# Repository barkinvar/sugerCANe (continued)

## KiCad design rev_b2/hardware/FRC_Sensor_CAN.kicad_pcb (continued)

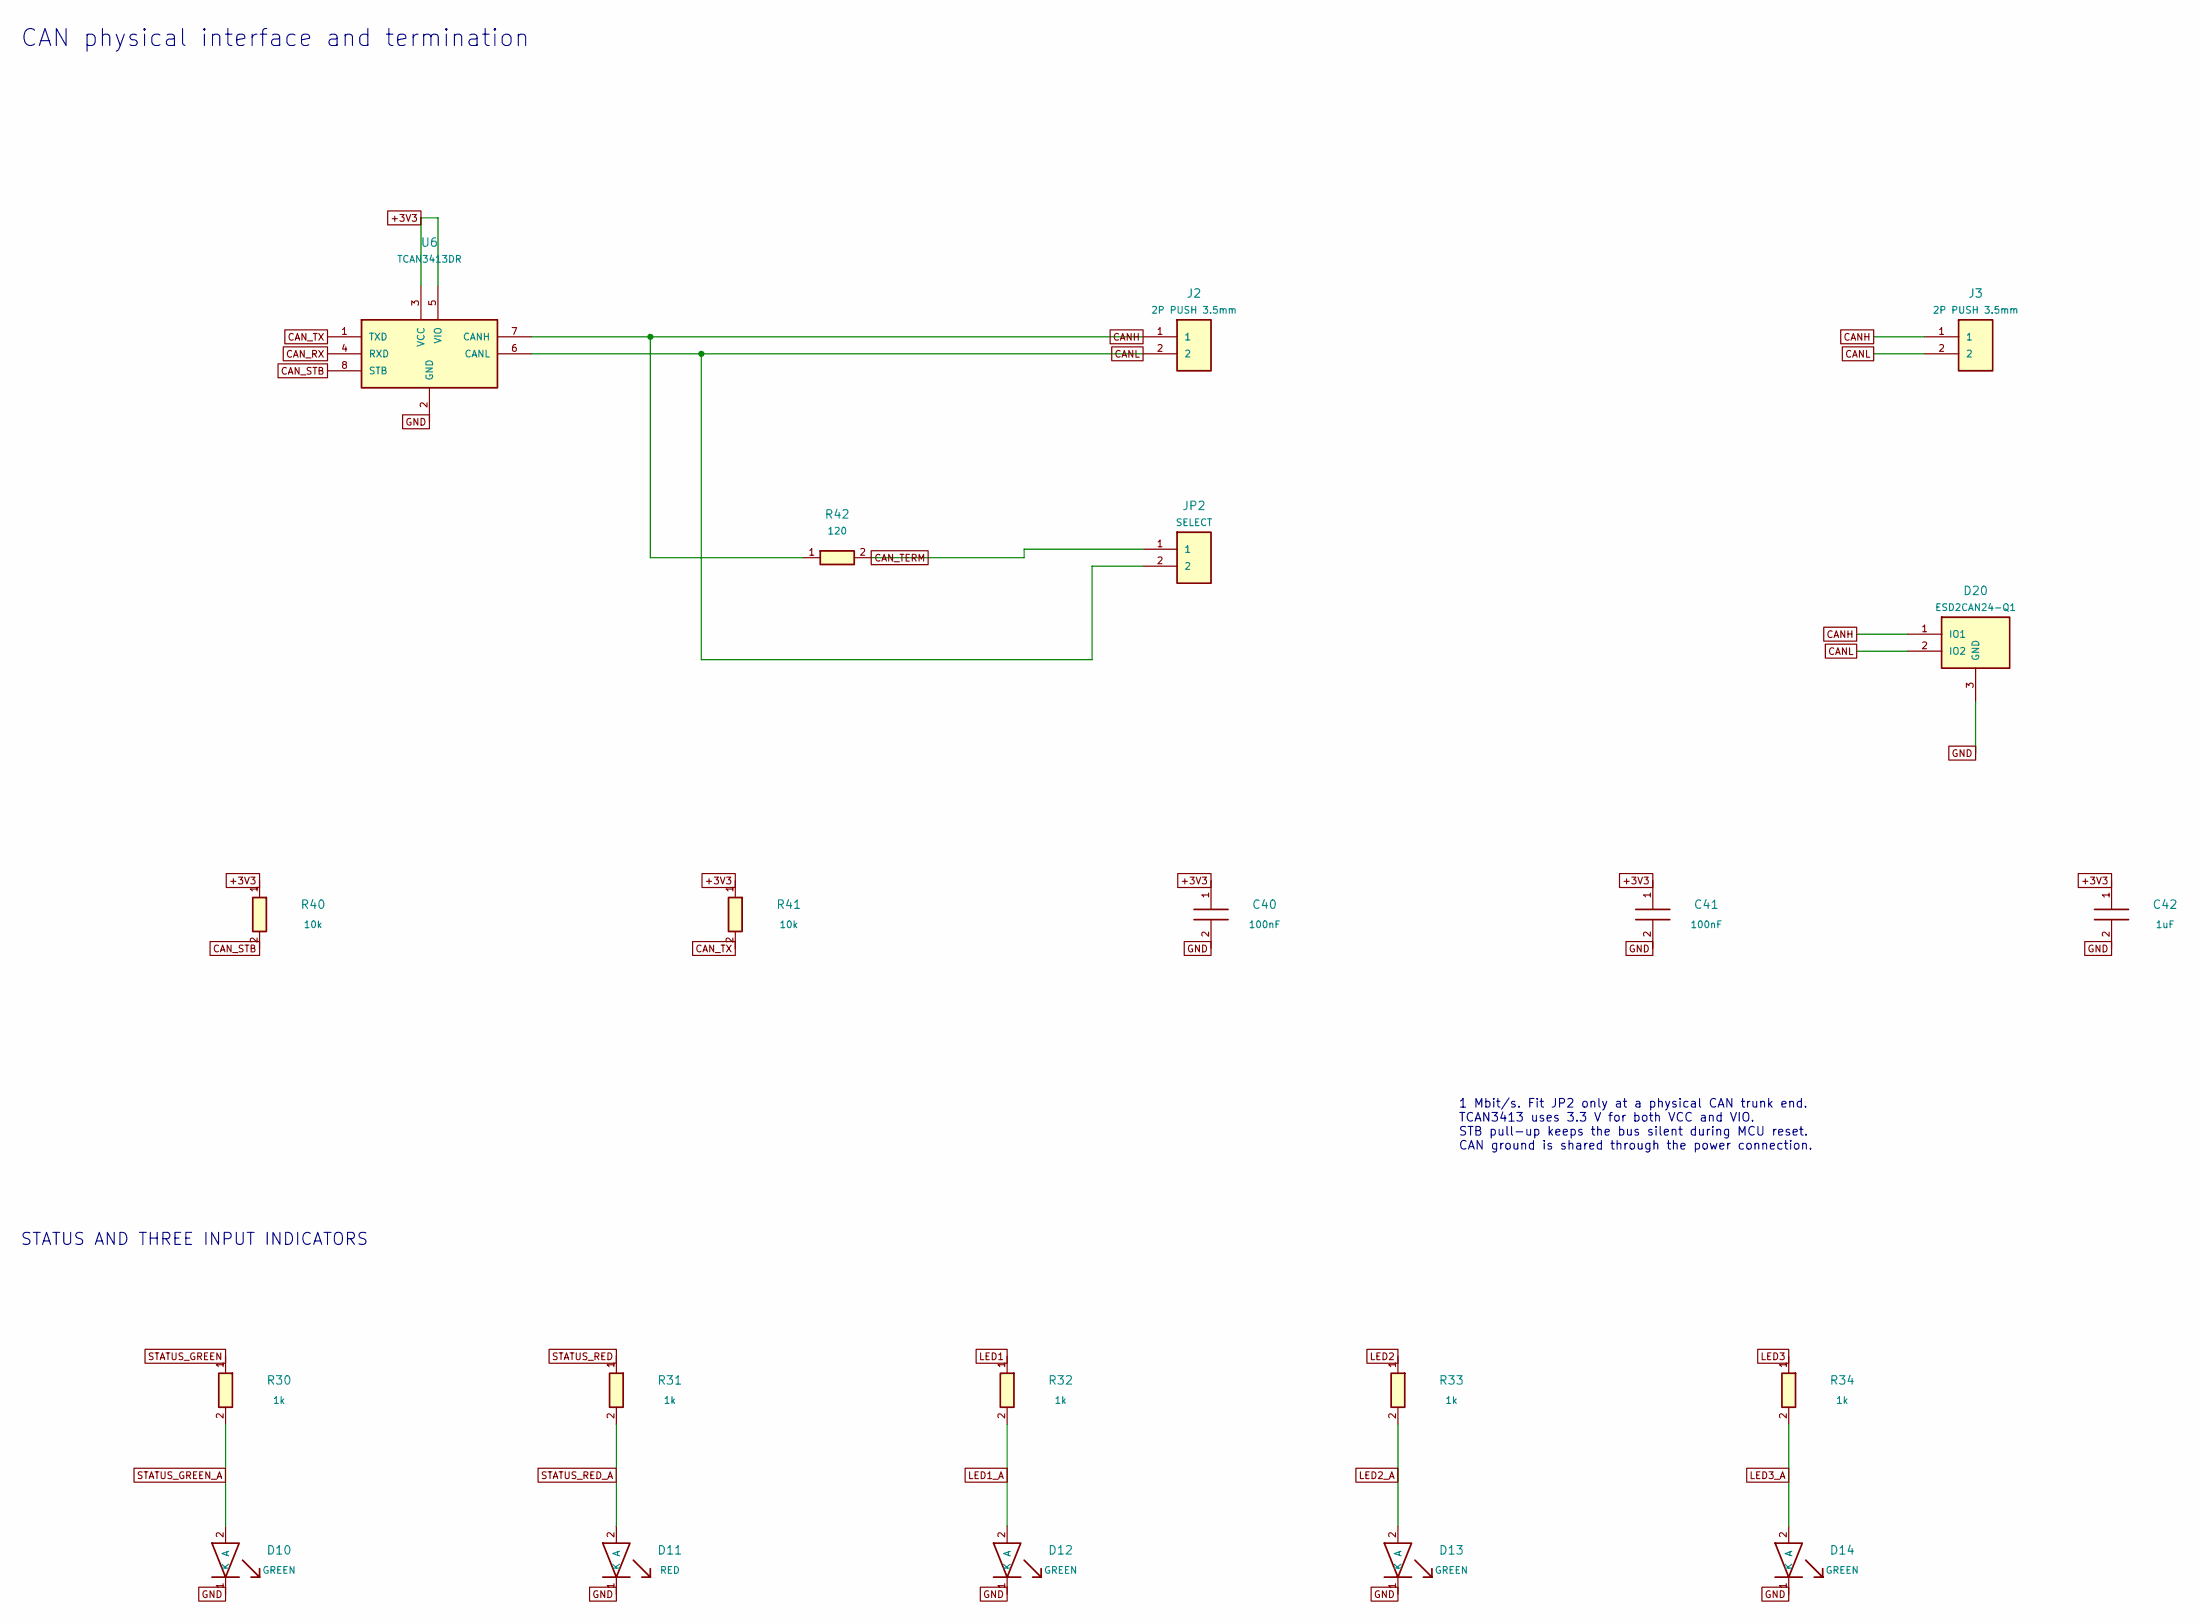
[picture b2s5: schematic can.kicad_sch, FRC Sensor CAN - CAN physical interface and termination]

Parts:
C40, C41: 100nF; C_0805_2012Metric; MPN CL21B104KCFNNNE
C42: 1uF; C_0805_2012Metric; MPN CC0805KKX7R9BB105
D10, D12, D13, D14: GREEN; LED_0805_2012Metric; MPN LTST-C170KGKT
D11: RED; LED_0805_2012Metric; MPN LTST-C170KRKT
D20: ESD2CAN24-Q1; SOT-23; MPN ESD2CAN24DBZRQ1
J2, J3: 2P PUSH 3.5mm; Weidmuller_LSF_90_2P; MPN 1824420000
JP2: SELECT; PinHeader_1x02_P2.00mm_Vertical; MPN M22-2010205
R30, R31, R32, R33, R34: 1k; R_0805_2012Metric; MPN 0805W8F1001T5E
R40, R41: 10k; R_0805_2012Metric; MPN 0805W8F1002T5E
R42: 120; R_1206_3216Metric; MPN RC1206FR-07120RL
U6: TCAN3413DR; SOIC-8_3.9x4.9mm_P1.27mm; MPN TCAN3413DR

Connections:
+3V3: C40.1, C41.1, C42.1, R40.1, R41.1, U6.3 (VCC), U6.5 (VIO); also elsewhere on the board
CANH: D20.1 (IO1), J2.1, J3.1, R42.1, U6.7 (CANH)
CANL: D20.2 (IO2), J2.2, J3.2, JP2.2, U6.6 (CANL)
CAN_RX: U6.4 (RXD); also elsewhere on the board
CAN_STB: R40.2, U6.8 (STB); also elsewhere on the board
CAN_TERM: JP2.1, R42.2
CAN_TX: R41.2, U6.1 (TXD); also elsewhere on the board
GND: C40.2, C41.2, C42.2, D10.1 (K), D11.1 (K), D12.1 (K), D13.1 (K), D14.1 (K), D20.3 (GND), U6.2 (GND); also elsewhere on the board
LED1: R32.1; also elsewhere on the board
LED1_A: D12.2 (A), R32.2
LED2: R33.1; also elsewhere on the board
LED2_A: D13.2 (A), R33.2
LED3: R34.1; also elsewhere on the board
LED3_A: D14.2 (A), R34.2
STATUS_GREEN: R30.1; also elsewhere on the board
STATUS_GREEN_A: D10.2 (A), R30.2
STATUS_RED: R31.1; also elsewhere on the board
STATUS_RED_A: D11.2 (A), R31.2

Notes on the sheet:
CAN physical interface and termination
1 Mbit/s. Fit JP2 only at a physical CAN trunk end. TCAN3413 uses 3.3 V for both VCC and VIO. STB pull-up keeps the bus silent during MCU reset. CAN ground is shared through the power connection.
STATUS AND THREE INPUT INDICATORS

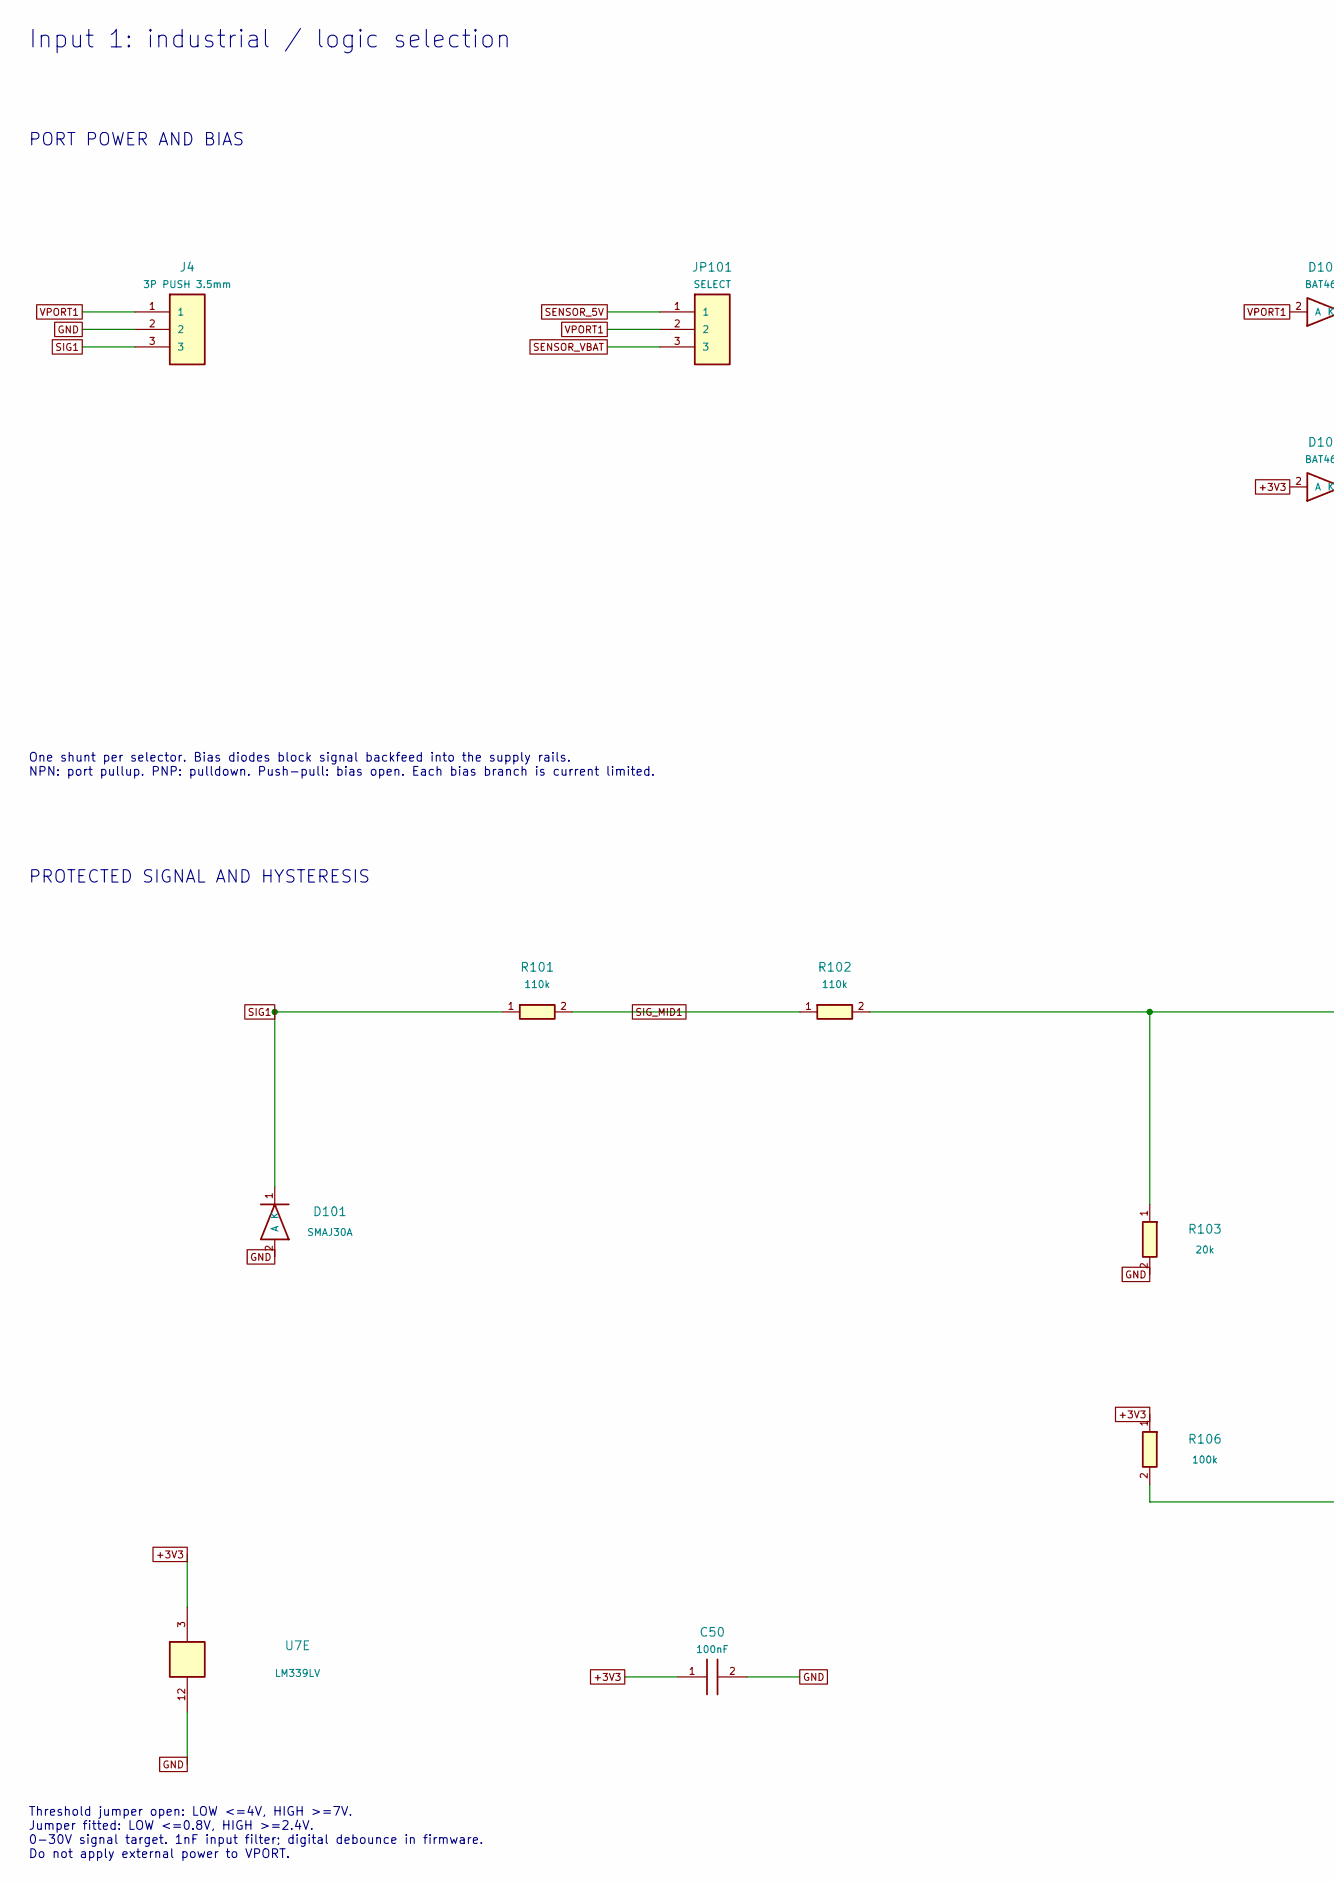
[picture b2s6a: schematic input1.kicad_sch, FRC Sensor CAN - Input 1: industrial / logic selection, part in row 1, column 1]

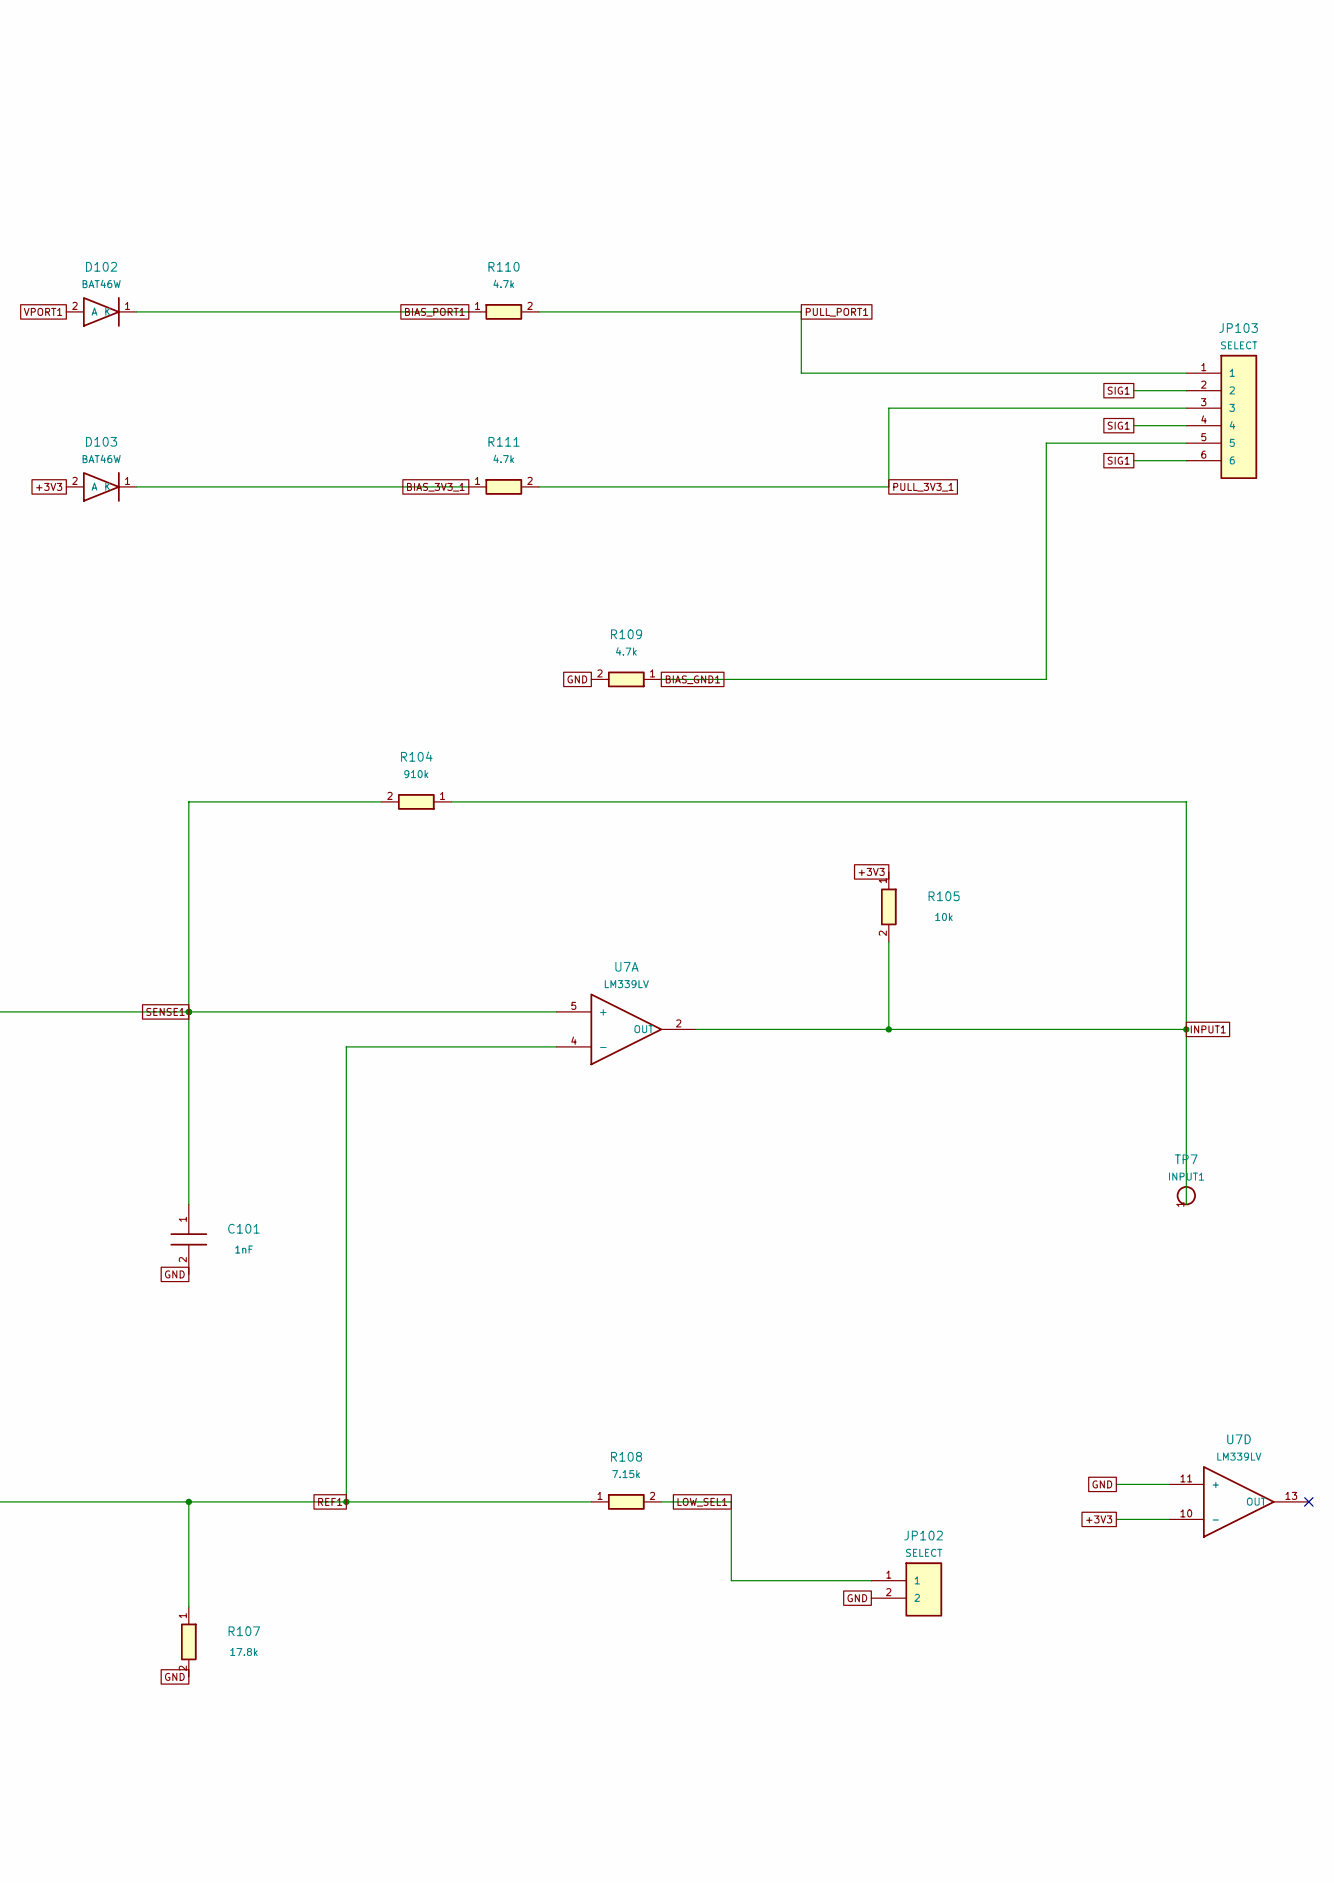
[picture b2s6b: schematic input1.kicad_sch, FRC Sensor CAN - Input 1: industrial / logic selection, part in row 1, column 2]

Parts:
C50: 100nF; C_0805_2012Metric; MPN CL21B104KCFNNNE
C101: 1nF; C_0805_2012Metric; MPN CC0805JRNPO9BN102
D101: SMAJ30A; D_SMA; MPN SMAJ30A
D102, D103: BAT46W; D_SOD-123; MPN BAT46W-E3-18
J4: 3P PUSH 3.5mm; Weidmuller_LSF_90_3P; MPN 1824430000
JP101: SELECT; PinHeader_1x03_P2.00mm_Vertical; MPN M22-2010305
JP102: SELECT; PinHeader_1x02_P2.00mm_Vertical; MPN M22-2010205
JP103: SELECT; PinHeader_2x03_P2.00mm_Vertical; MPN M22-2020305
R101, R102: 110k; R_0805_2012Metric; MPN RC0805FR-07110KL
R103: 20k; R_0805_2012Metric; MPN RC0805FR-0720KL
R104: 910k; R_0805_2012Metric; MPN RC0805FR-07910KL
R105: 10k; R_0805_2012Metric; MPN 0805W8F1002T5E
R106: 100k; R_0805_2012Metric; MPN 0805W8F1003T5E
R107: 17.8k; R_0805_2012Metric; MPN ERJ-6ENF1782V
R108: 7.15k; R_0805_2012Metric; MPN RC0805FR-077K15L
R109: 4.7k; R_2010_5025Metric; MPN RC2010FK-074K7L
R110, R111: 4.7k; R_0805_2012Metric; MPN 0805W8F4701T5E
TP7: INPUT1; TestPoint_Pad_D2.0mm
U7: LM339LV; SOIC-14_3.9x8.7mm_P1.27mm; MPN LM339LVDR

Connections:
+3V3: C50.1, D103.2 (A), R105.1, R106.1, U7.3, U7.10 (-); also elsewhere on the board
BIAS_3V3_1: D103.1 (K), R111.1
BIAS_GND1: JP103.5, R109.1
BIAS_PORT1: D102.1 (K), R110.1
GND: C50.2, C101.2, D101.2 (A), J4.2, JP102.2, R103.2, R107.2, R109.2, U7.11 (+), U7.12; also elsewhere on the board
INPUT1: R104.1, R105.2, TP7.1, U7.2 (OUT); also elsewhere on the board
LOW_SEL1: JP102.1, R108.2
PULL_3V3_1: JP103.3, R111.2
PULL_PORT1: JP103.1, R110.2
REF1: R106.2, R107.1, R108.1, U7.4 (-)
SENSE1: C101.1, R102.2, R103.1, R104.2, U7.5 (+)
SENSOR_5V: JP101.1; also elsewhere on the board
SENSOR_VBAT: JP101.3; also elsewhere on the board
SIG1: D101.1 (K), J4.3, JP103.2, JP103.4, JP103.6, R101.1
SIG_MID1: R101.2, R102.1
VPORT1: D102.2 (A), J4.1, JP101.2

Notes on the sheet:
Input 1: industrial / logic selection
PORT POWER AND BIAS
One shunt per selector. Bias diodes block signal backfeed into the supply rails. NPN: port pullup. PNP: pulldown. Push-pull: bias open. Each bias branch is current limited.
PROTECTED SIGNAL AND HYSTERESIS
Threshold jumper open: LOW <=4V, HIGH >=7V. Jumper fitted: LOW <=0.8V, HIGH >=2.4V. 0-30V signal target. 1nF input filter; digital debounce in firmware. Do not apply external power to VPORT.

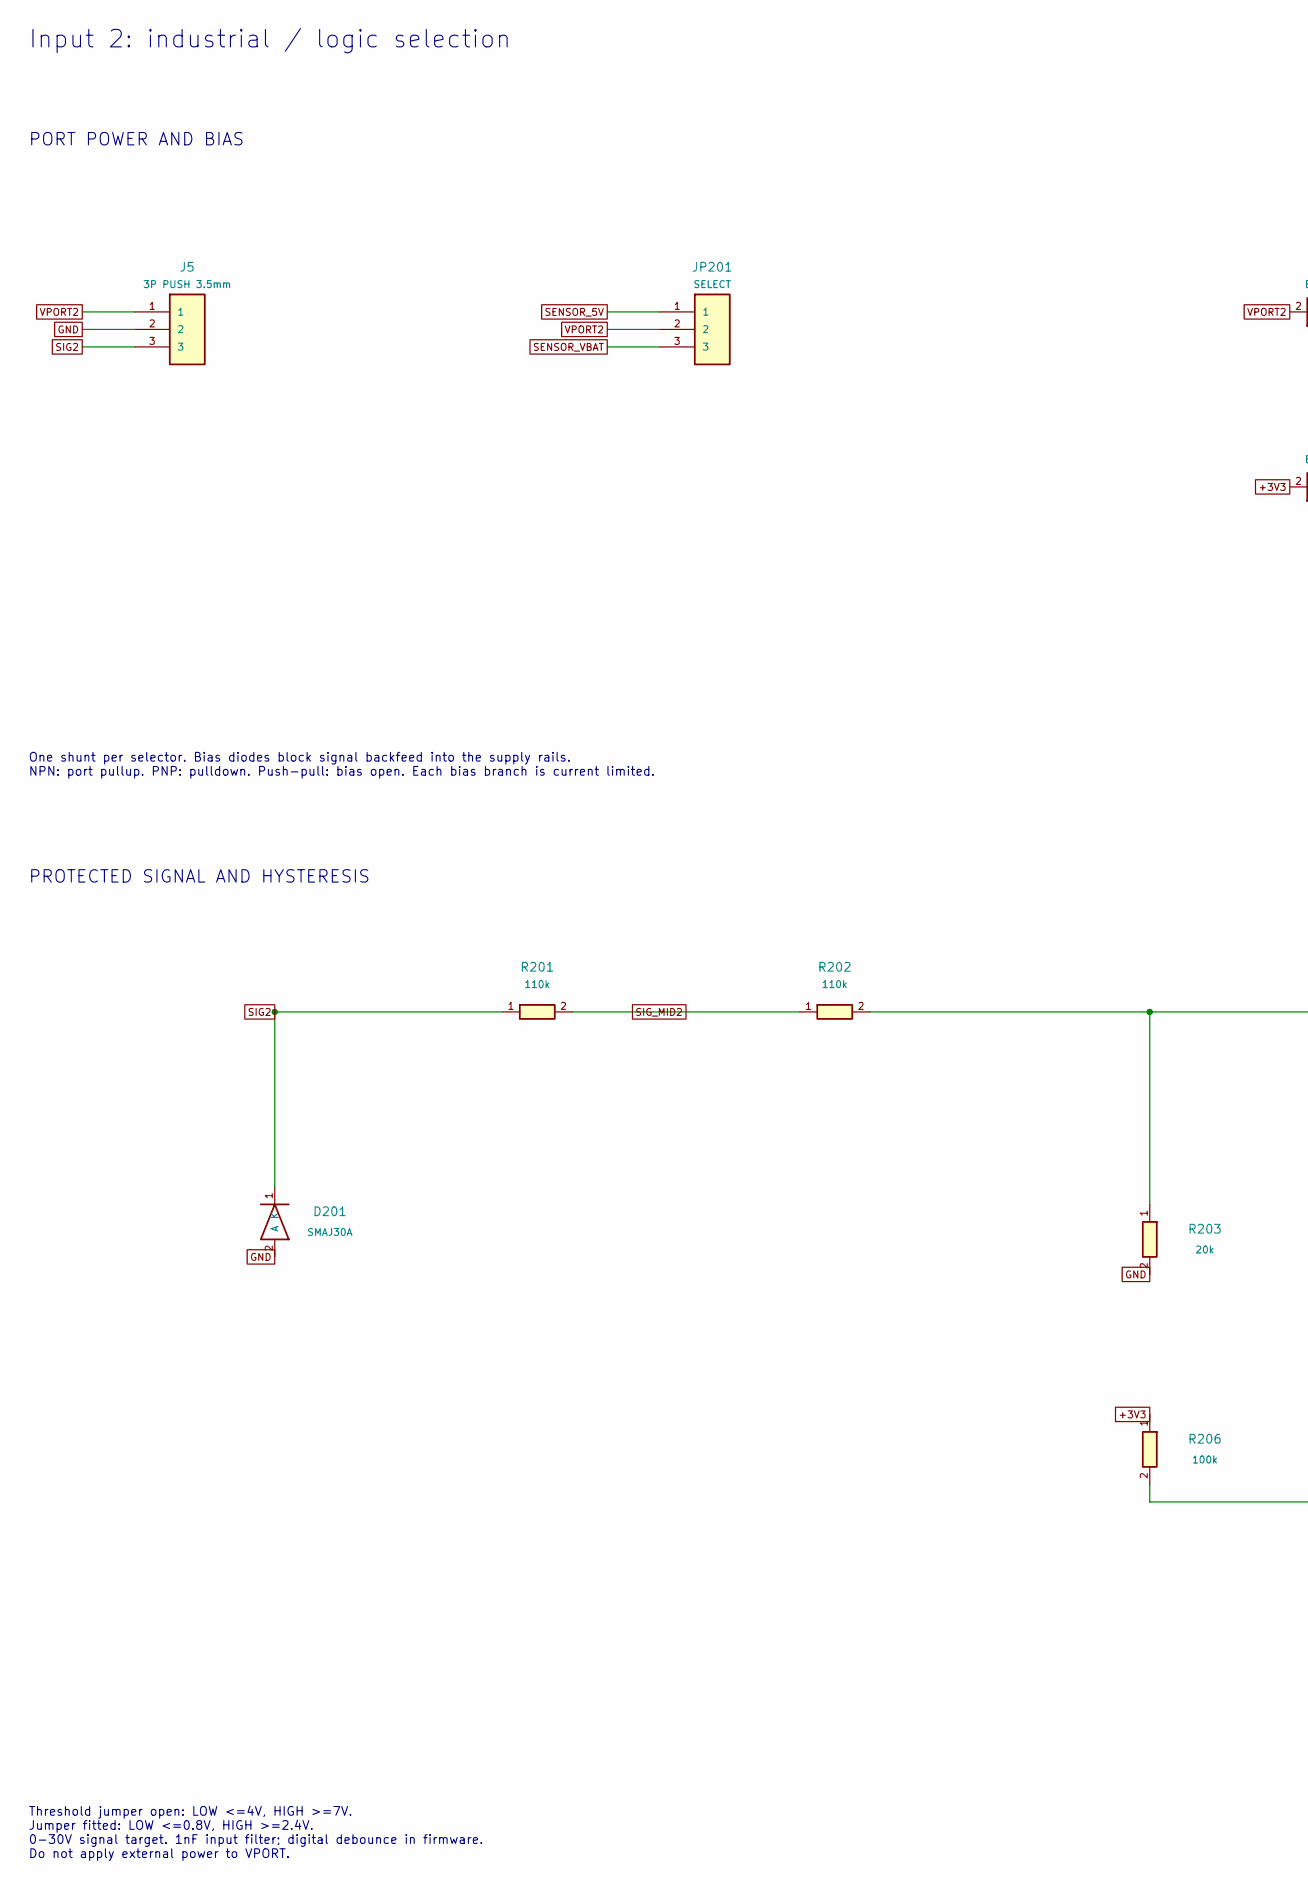
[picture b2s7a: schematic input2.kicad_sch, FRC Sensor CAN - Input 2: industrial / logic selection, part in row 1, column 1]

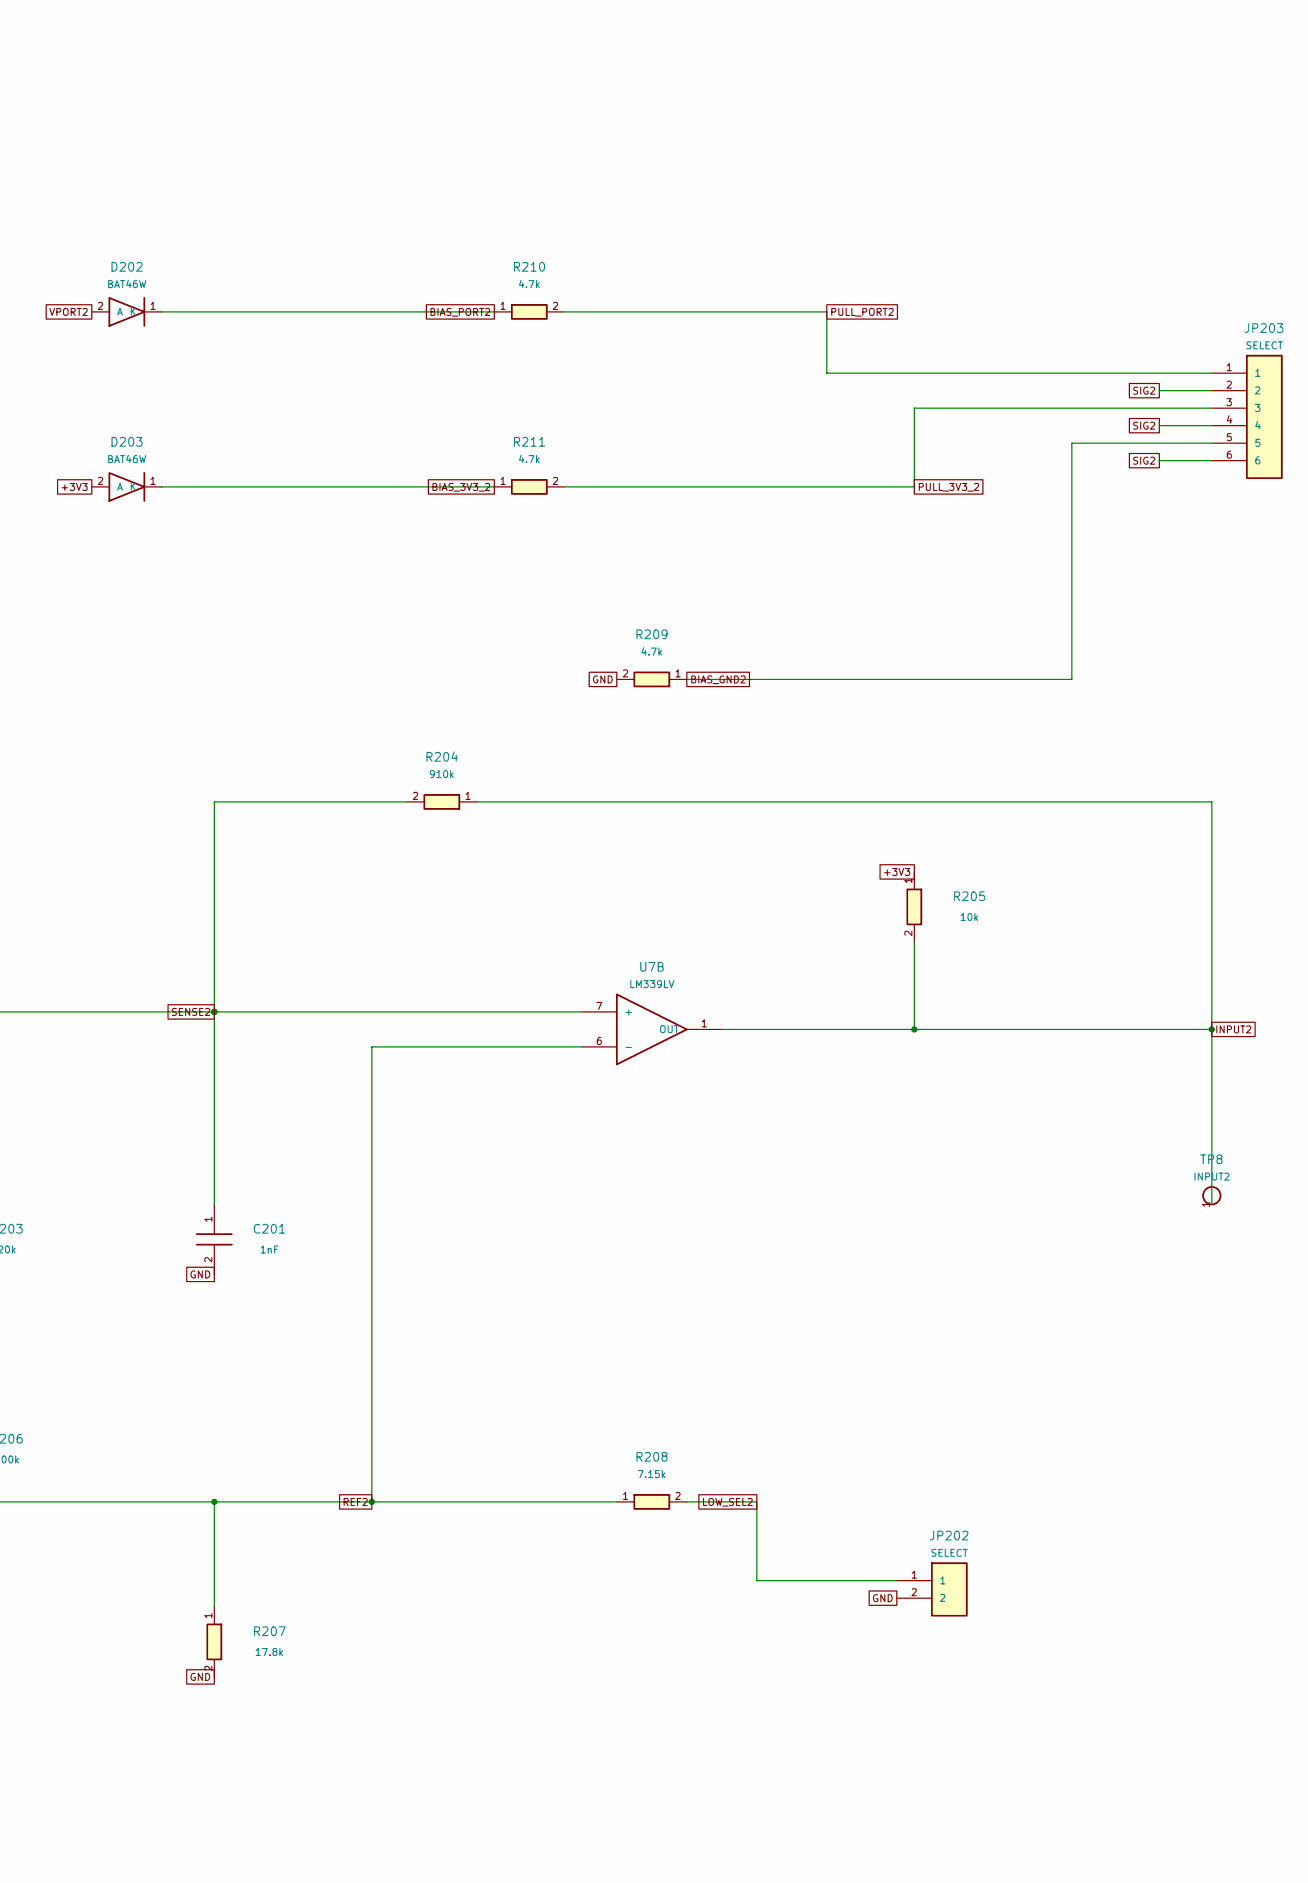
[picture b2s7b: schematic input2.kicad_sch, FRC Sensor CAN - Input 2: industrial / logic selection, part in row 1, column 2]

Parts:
C201: 1nF; C_0805_2012Metric; MPN CC0805JRNPO9BN102
D201: SMAJ30A; D_SMA; MPN SMAJ30A
D202, D203: BAT46W; D_SOD-123; MPN BAT46W-E3-18
J5: 3P PUSH 3.5mm; Weidmuller_LSF_90_3P; MPN 1824430000
JP201: SELECT; PinHeader_1x03_P2.00mm_Vertical; MPN M22-2010305
JP202: SELECT; PinHeader_1x02_P2.00mm_Vertical; MPN M22-2010205
JP203: SELECT; PinHeader_2x03_P2.00mm_Vertical; MPN M22-2020305
R201, R202: 110k; R_0805_2012Metric; MPN RC0805FR-07110KL
R203: 20k; R_0805_2012Metric; MPN RC0805FR-0720KL
R204: 910k; R_0805_2012Metric; MPN RC0805FR-07910KL
R205: 10k; R_0805_2012Metric; MPN 0805W8F1002T5E
R206: 100k; R_0805_2012Metric; MPN 0805W8F1003T5E
R207: 17.8k; R_0805_2012Metric; MPN ERJ-6ENF1782V
R208: 7.15k; R_0805_2012Metric; MPN RC0805FR-077K15L
R209: 4.7k; R_2010_5025Metric; MPN RC2010FK-074K7L
R210, R211: 4.7k; R_0805_2012Metric; MPN 0805W8F4701T5E
TP8: INPUT2; TestPoint_Pad_D2.0mm
U7: LM339LV; SOIC-14_3.9x8.7mm_P1.27mm; MPN LM339LVDR

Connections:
+3V3: D203.2 (A), R205.1, R206.1; also elsewhere on the board
BIAS_3V3_2: D203.1 (K), R211.1
BIAS_GND2: JP203.5, R209.1
BIAS_PORT2: D202.1 (K), R210.1
GND: C201.2, D201.2 (A), J5.2, JP202.2, R203.2, R207.2, R209.2; also elsewhere on the board
INPUT2: R204.1, R205.2, TP8.1, U7.1 (OUT); also elsewhere on the board
LOW_SEL2: JP202.1, R208.2
PULL_3V3_2: JP203.3, R211.2
PULL_PORT2: JP203.1, R210.2
REF2: R206.2, R207.1, R208.1, U7.6 (-)
SENSE2: C201.1, R202.2, R203.1, R204.2, U7.7 (+)
SENSOR_5V: JP201.1; also elsewhere on the board
SENSOR_VBAT: JP201.3; also elsewhere on the board
SIG2: D201.1 (K), J5.3, JP203.2, JP203.4, JP203.6, R201.1
SIG_MID2: R201.2, R202.1
VPORT2: D202.2 (A), J5.1, JP201.2

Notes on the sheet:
Input 2: industrial / logic selection
PORT POWER AND BIAS
One shunt per selector. Bias diodes block signal backfeed into the supply rails. NPN: port pullup. PNP: pulldown. Push-pull: bias open. Each bias branch is current limited.
PROTECTED SIGNAL AND HYSTERESIS
Threshold jumper open: LOW <=4V, HIGH >=7V. Jumper fitted: LOW <=0.8V, HIGH >=2.4V. 0-30V signal target. 1nF input filter; digital debounce in firmware. Do not apply external power to VPORT.
